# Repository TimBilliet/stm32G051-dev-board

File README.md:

# stm32G051-dev-board

Simple PCB I made for testing the STM32G051C6U6 microcontroller.\
Designed in KiCad and manufactured by JLCPCB.\
All pins are broken out.

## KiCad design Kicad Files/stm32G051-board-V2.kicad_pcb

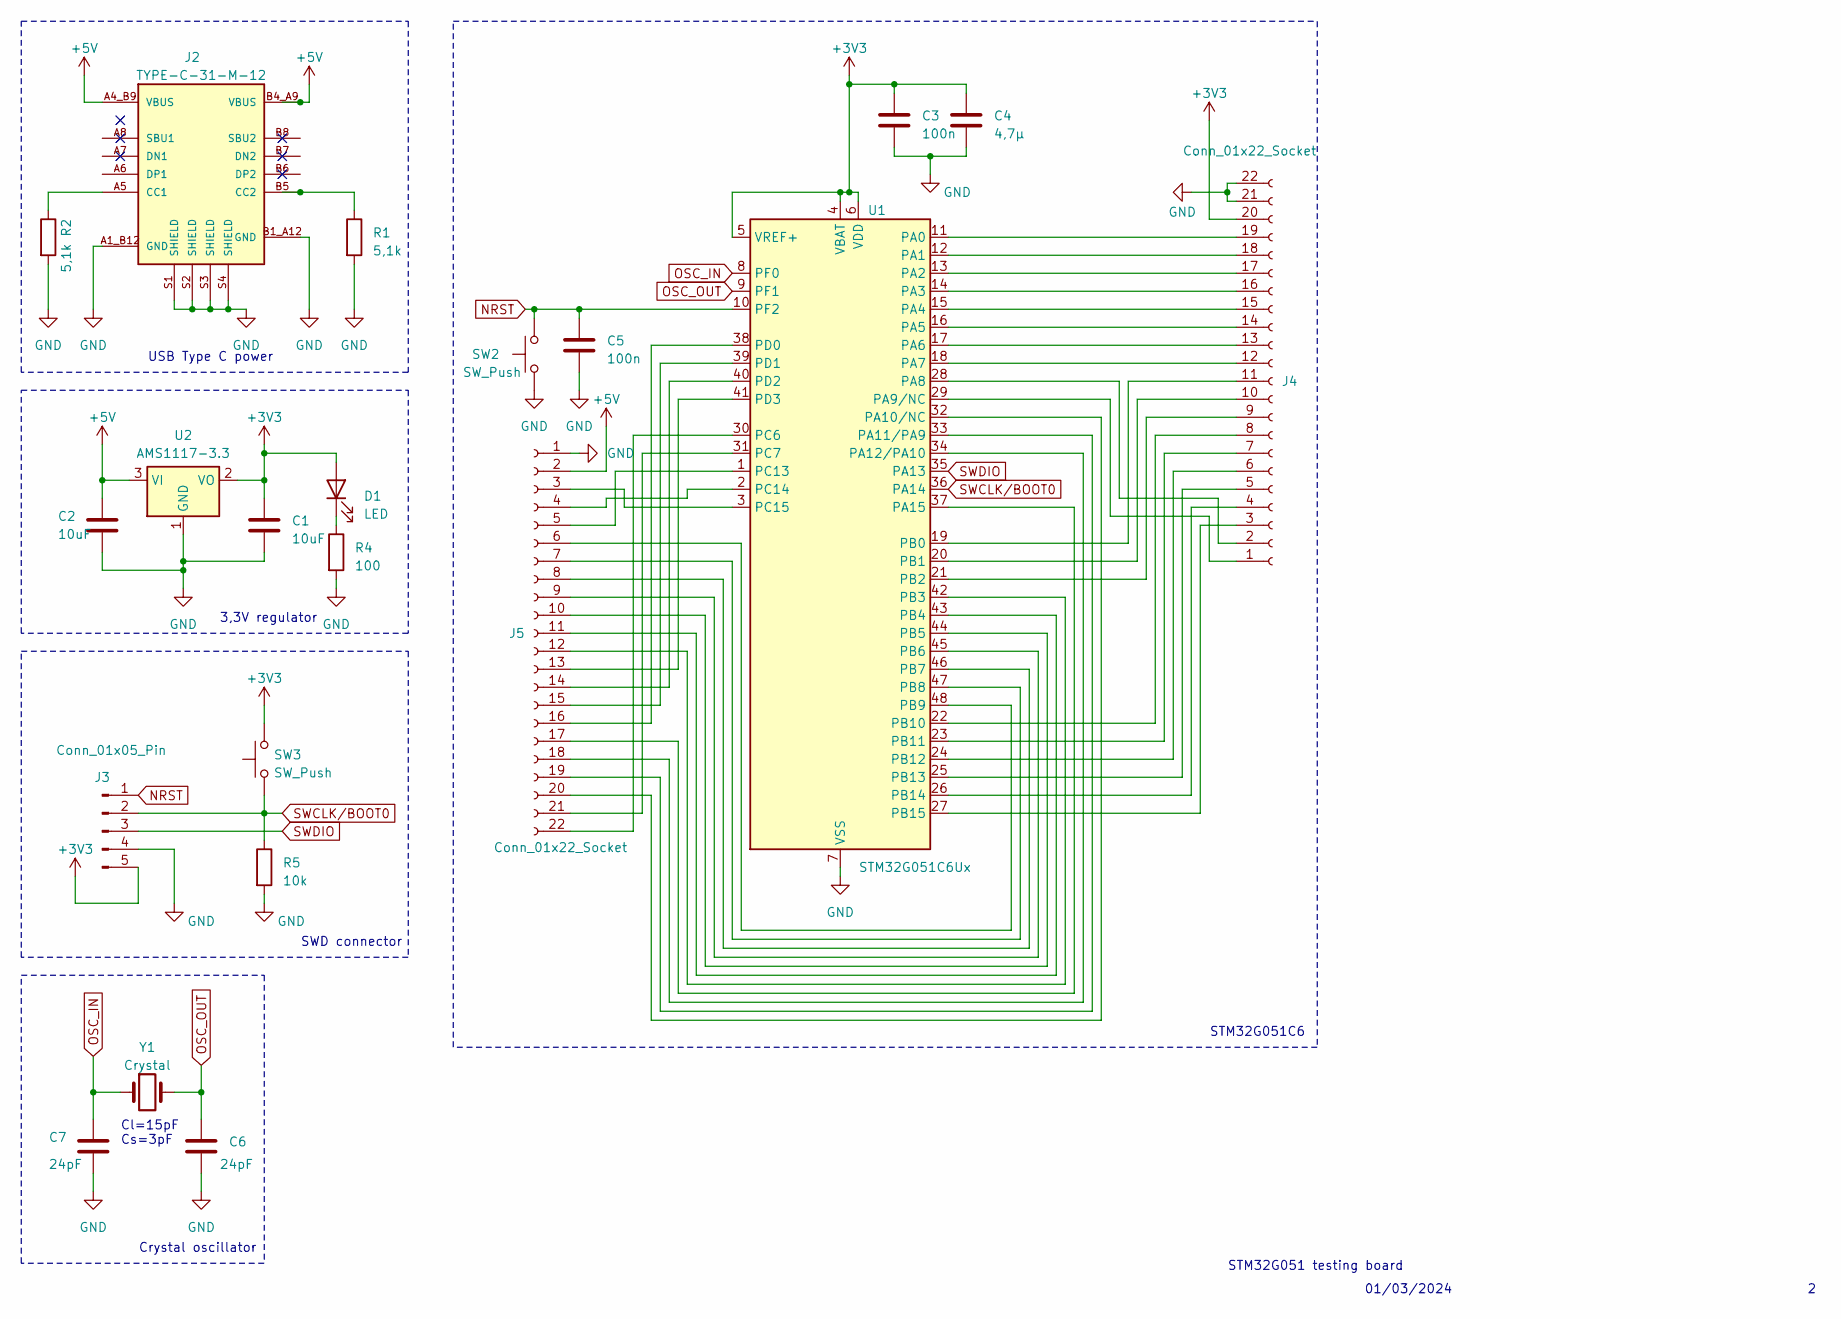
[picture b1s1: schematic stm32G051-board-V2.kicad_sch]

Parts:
C1, C2: 10uF; C_0603_1608Metric
C3, C5: 100n; C_0603_1608Metric
C4: 4,7µ; C_0603_1608Metric
C6, C7: 24pF; C_0603_1608Metric
D1: LED; LED_0603_1608Metric
J2: TYPE-C-31-M-12; HRO_TYPE-C-31-M-12; PARTREV 2020.12.08
J3: Conn_01x05_Pin; PinHeader_1x05_P2.54mm_Vertical
J4, J5: Conn_01x22_Socket; PinSocket_1x22_P2.54mm_Vertical
R1, R2: 5,1k; R_0805_2012Metric
R4: 100; R_0603_1608Metric
R5: 10k; R_0603_1608Metric
SW2, SW3: SW_Push; TS1088R02026
U1: STM32G051C6Ux; QFN-48-1EP_7x7mm_P0.5mm_EP5.6x5.6mm
U2: AMS1117-3.3; SOT-223-3_TabPin2
Y1: Crystal; Crystal_SMD_3225-4Pin_3.2x2.5mm

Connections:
+3V3: C1.1, C3.1, C4.1, D1.2 (A), J3.5, J4.20, SW3.2, U1.4 (VBAT), U1.5 (VREF+), U1.6 (VDD), U2.2 (VO)
+5V: C2.1, J2.A4_B9 (VBUS), J2.B4_A9 (VBUS), J5.2, U2.3 (VI)
GND: C1.2, C2.2, C3.2, C4.2, C5.2, C6.2, C7.2, J2.A1_B12 (GND), J2.B1_A12 (GND), J2.S1 (SHIELD), J2.S2 (SHIELD), J2.S3 (SHIELD), J2.S4 (SHIELD), J3.4, J4.21, J4.22, J5.1, R1.2, R2.2, R4.2, R5.2, SW2.1, U1.7 (VSS), U1.49 (VSS), U2.1 (GND)
NRST: C5.1, J3.1, SW2.2, U1.10 (PF2)
unnamed: D1.1 (K), R4.1
unnamed: J2.A5 (CC1), R2.1
unnamed: J2.B5 (CC2), R1.1
unnamed: J4.1, U1.29 (PA9/NC)
unnamed: J4.2, U1.28 (PA8)
unnamed: J4.3, U1.27 (PB15)
unnamed: J4.4, U1.26 (PB14)
unnamed: J4.5, U1.25 (PB13)
unnamed: J4.6, U1.24 (PB12)
unnamed: J4.7, U1.23 (PB11)
unnamed: J4.8, U1.22 (PB10)
unnamed: J4.9, U1.21 (PB2)
unnamed: J4.10, U1.20 (PB1)
unnamed: J4.11, U1.19 (PB0)
unnamed: J4.12, U1.18 (PA7)
unnamed: J4.13, U1.17 (PA6)
unnamed: J4.14, U1.16 (PA5)
unnamed: J4.15, U1.15 (PA4)
unnamed: J4.16, U1.14 (PA3)
unnamed: J4.17, U1.13 (PA2)
unnamed: J4.18, U1.12 (PA1)
unnamed: J4.19, U1.11 (PA0)
unnamed: J5.3, U1.3 (PC15)
unnamed: J5.4, U1.2 (PC14)
unnamed: J5.5, U1.1 (PC13)
unnamed: J5.6, U1.48 (PB9)
unnamed: J5.7, U1.47 (PB8)
unnamed: J5.8, U1.46 (PB7)
unnamed: J5.9, U1.45 (PB6)
unnamed: J5.10, U1.44 (PB5)
unnamed: J5.11, U1.43 (PB4)
unnamed: J5.12, U1.42 (PB3)
unnamed: J5.13, U1.41 (PD3)
unnamed: J5.14, U1.40 (PD2)
unnamed: J5.15, U1.39 (PD1)
unnamed: J5.16, U1.38 (PD0)
unnamed: J5.17, U1.37 (PA15)
unnamed: J5.18, U1.34 (PA12/PA10)
unnamed: J5.19, U1.33 (PA11/PA9)
unnamed: J5.20, U1.32 (PA10/NC)
unnamed: J5.21, U1.31 (PC7)
unnamed: J5.22, U1.30 (PC6)
OSC_IN: C7.1, U1.8 (PF0), Y1.1
OSC_OUT: C6.1, U1.9 (PF1), Y1.3
SWCLK/BOOT0: J3.2, R5.1, SW3.1, U1.36 (PA14)
SWDIO: J3.3, U1.35 (PA13)

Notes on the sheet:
STM32G051 testing board
STM32G051C6
SWD connector
USB Type C power
Crystal oscillator
01/03/2024
Cl=15pF Cs=3pF
3,3V regulator

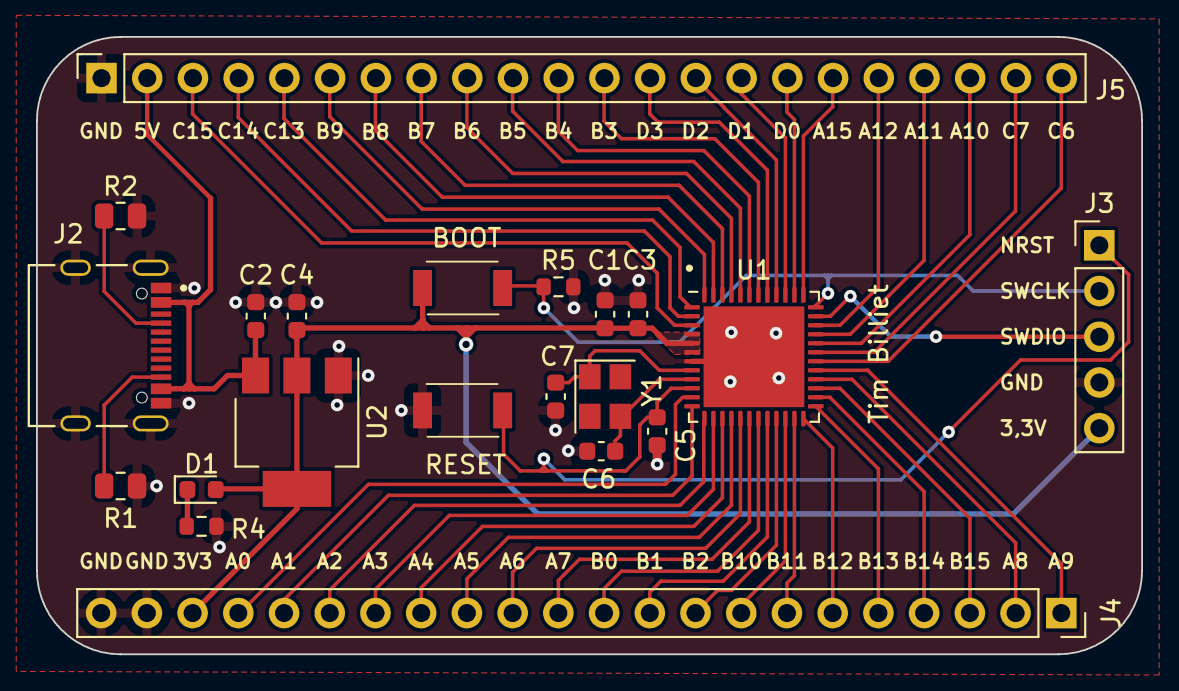
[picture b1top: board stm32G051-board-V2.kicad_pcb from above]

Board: 2 copper layers, 61.4 x 34.3 mm, 21 parts (0 on the bottom side), 50 nets.

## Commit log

2024-04-28 added kicad files and schematic pdf
